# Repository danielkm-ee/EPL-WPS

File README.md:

# Spark EDM: An EDM power supply for hobby CNCs

A high-efficiency power supply unit designed for Electrical Discharge Machining (EDM) applications. The design is based on the Rack Robotics Powercore V3 and owes much to their engineering efforts.

## EPL Contributions

The EPL has reworked a few aspects of the Rack Robotics Powercore V3 for use in it's CNC-Type Wire EDM. Primarily, we've made use of 2.54mm pin headers in place of the spring-based connectors, or Pogo pins, to simplify construction without the enclosure. Other modifications have been made the the firmware project structure, separating sensor drivers, boost converter, fault handling, and other portions of the project into a modular C++ library. We have also implemented a frequency-coded feedback signal for compatibility with encoder and edge counting inputs available on many CNC control boards.

If you would like to explore or purchase the original PowerCore V3, please vist Rack Robotics at

and

# Repository Structure

```
├── docs               - documentation files & repository resources
│   ├── img                - images for README.md's
│   ├── LTSpice            - LTSpice Simulations
│   └── schematics         - pdfs of the schematics
├── firmware           - firmware project and library based on the PicoSDK
│   ├── docs               - docs for the firmware
│   ├── feedback_test      - firmware which outputs a frequency sweep for feedback testing
│   ├── src                - source files for the Spark EDM firmware
│   └── tpl0401b_test      - test firmware for testing the boost module potentiometer
├── hardware           - hardware resources for PCBs and the enclosure
│   ├── CAD                - CAD resources for enclosure design & system documentation
│   ├── circuit-boards     - circuit boards for the Spark EDM
│   └── KiCAD-library      - KiCAD library for the Spark EDM
└── tools              - tools for flashing & communicating with the Spark EDM
```

# Building the EDM Supply
The Spark EDM is not available for purchase through the EPL or any other means, but access to the manufacturing resources are provided for those with experience ordering and building up PCBs through the likes of JLCPCB, Oshpark, or PCBWay.

# LICENSE 
This project is based on Powercore V3 by Rack Robotics, Inc., used under CC BY-NC-SA 4.0.

Original copyright: © 2025 Rack Robotics, Inc.

Modifications and additions by Portland State University Electronics Prototyping Lab (PSU EPL) are also licensed under CC BY-NC-SA 4.0.

## Changes from Original
* Firmare:
    * Migration from Arduino to pure PicoSDK
    * new project structure and firmware documetation
    * frequency-coded feedback signal
    * testing firmware for the tpl10401b
    * tools for flashing and communicating with the device
    * extended command line interface with commands for setting the gap voltage and machining frequency
    * conventionalized responses from the serial interface for debugging
    * modularized library for the various functions of the power supply for extendability
    * fault handler and context management utilities
* Hardware:
    * Replacement of the RackRobotics and PowercoreV3 logo in compliance with copyright restrictions
    * Use of 2.54mm headers in place of spring-loaded connectors for ease of assembly
    * Removal of thermal reliefs on high-current capacitors in the pi-filter and boost converter module
    * Layout changes with larger trace widths for high current lines
    * Adaptations for 2.54mm connectors
    * Edge cutout for Pi Pico micro-USB and testpoints
    * Updated component values for missing JCL & digikey part numbers
* Documentation
    * Updated schematics reflecting changes in PCB implementation
    * Firmware documentation reflecting new library, developers manual, and coding conventions for maintenence and new feature introduction
    * Developer's notes from capstone members at Portland State University

## You are free to:
* Share — copy and redistribute the material in any medium or format
* Adapt — remix, transform, and build upon the material

### Under the following terms:
* **Attribution** — You must give appropriate credit, provide a link to the license, and indicate if changes were made
* **NonCommercial** — You may not use the material for commercial purposes
* **ShareAlike** — If you remix, transform, or build upon the material, you must distribute your contributions under the same license

For the full license text, see: https://creativecommons.org/licenses/by-nc-sa/4.0/

### Notices:
You do not have to comply with the license for elements of the material in the public domain or where your use is permitted by an applicable exception or limitation.

No warranties are given. The license may not give you all of the permissions necessary for your intended use. For example, other rights such as publicity, privacy, or moral rights may limit how you use the material.

For the full license text, see: https://creativecommons.org/licenses/by-nc-sa/4.0/

This includes all hardware designs, firmware, documentation, and associated files in this repository. Commercial use requires explicit written permission from the project maintainers.

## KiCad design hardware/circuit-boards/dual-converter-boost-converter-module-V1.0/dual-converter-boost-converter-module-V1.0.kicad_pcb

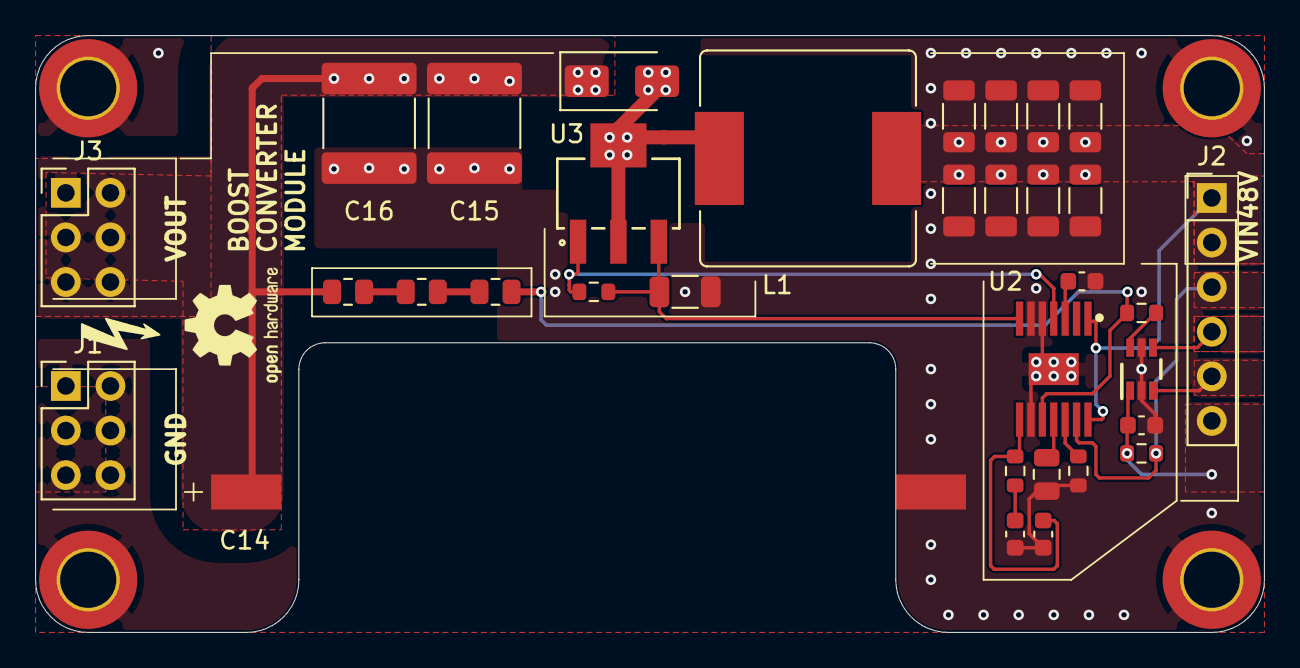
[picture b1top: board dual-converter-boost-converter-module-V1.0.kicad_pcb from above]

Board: 4 copper layers, 70.0 x 34.0 mm, 37 parts (0 on the bottom side), 19 nets.

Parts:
C1, C2, C3, C4, C6, C7, C8, C9: 10 uF; C_1206_3216Metric
C5, C10: 1 uF; C_0603_1608Metric
C11: 33 uF; C_0805_2012Metric
C12: 39nF; C_0603_1608Metric
C13: F; C_0603_1608Metric
C14: 22UF; 226TTA350M
C15, C16: 2.2 uF; C_2220_5750Metric
D1: US1M-13-F; D_SMA
H1, H2, H3, H4: M3_DIN; MountingHole_3.2mm_M3_DIN965_Pad_TopBottom
J1, J3: Vout Conn; PinHeader_2x03_P2.54mm_Vertical
J2: Conn_01x06; PinHeader_1x06_P2.54mm_Vertical
L1: 680 uH; SRR1210-681M
R1, R2, R3: 200K; R_0805_2012Metric
R4, R5: 2.2K; R_0603_1608Metric
R6: 49.3K; R_0603_1608Metric
R7: 15K; R_0603_1608Metric
R8: 100K; R_0603_1608Metric
R9: 90mR; R_1206_3216Metric
U1: TPL0401B-10DCKR
U2: LM5156HPWPR; lm5156h
U3: STN3N40K3

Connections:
+3.3V: C5.1, J2.6, R5.1, U1.1 (VDD)
+48V: C1.1, C2.1, C3.1, C4.1, C6.1, C7.1, C8.1, C9.1, J2.1, J2.2, L1.1, U2.1 (BIAS), U2.14 (EN_UVLO_SYNC)
/BOOST_PGOOD: J2.3, R5.2, U2.13 (PGOOD)
/BOOST_SWITCH_NET: D1.2 (A), L1.2, U3.2 (D), U3.4 (D)
/COMPENSATION: C13.1, R7.1, U2.8 (COMP)
/COUT_BOOST: C14.1, C15.1, C16.1, D1.1 (K), J3.1, J3.2, J3.3, J3.4, J3.5, J3.6, R1.1
/CURRENT_SENSE: R8.2, R9.1, U2.7 (CS), U3.3 (S)
/GATE_NET: R8.1, U2.4 (GATE), U3.1 (G)
/V_FEEDBACK: R3.2, R4.2, U2.10 (FB)
GND: C1.2, C2.2, C3.2, C4.2, C5.2, C6.2, C7.2, C8.2, C9.2, C10.2, C11.2, C12.2, C13.2, C14.2, C15.2, C16.2, H1.1, H2.1, H3.1, H4.1, J1.1, J1.2, J1.3, J1.4, J1.5, J1.6, R6.2, R9.2, U1.2 (GND), U1.5 (W), U2.5 (PGND), U2.6 (AGND), U2.9 (DITHOFF), U2.15 (EP)
unnamed: C12.1, R7.2
unnamed: J2.4, U1.4 (SDA)
unnamed: J2.5, U1.3 (SCL)
unnamed: R1.2, R2.1
unnamed: R2.2, R3.1
unnamed: R4.1, U1.6 (H)
unnamed: R6.1, U2.12 (RT)
unnamed: C11.1, U2.11 (SS)
unnamed: C10.1, U2.3 (VCC)

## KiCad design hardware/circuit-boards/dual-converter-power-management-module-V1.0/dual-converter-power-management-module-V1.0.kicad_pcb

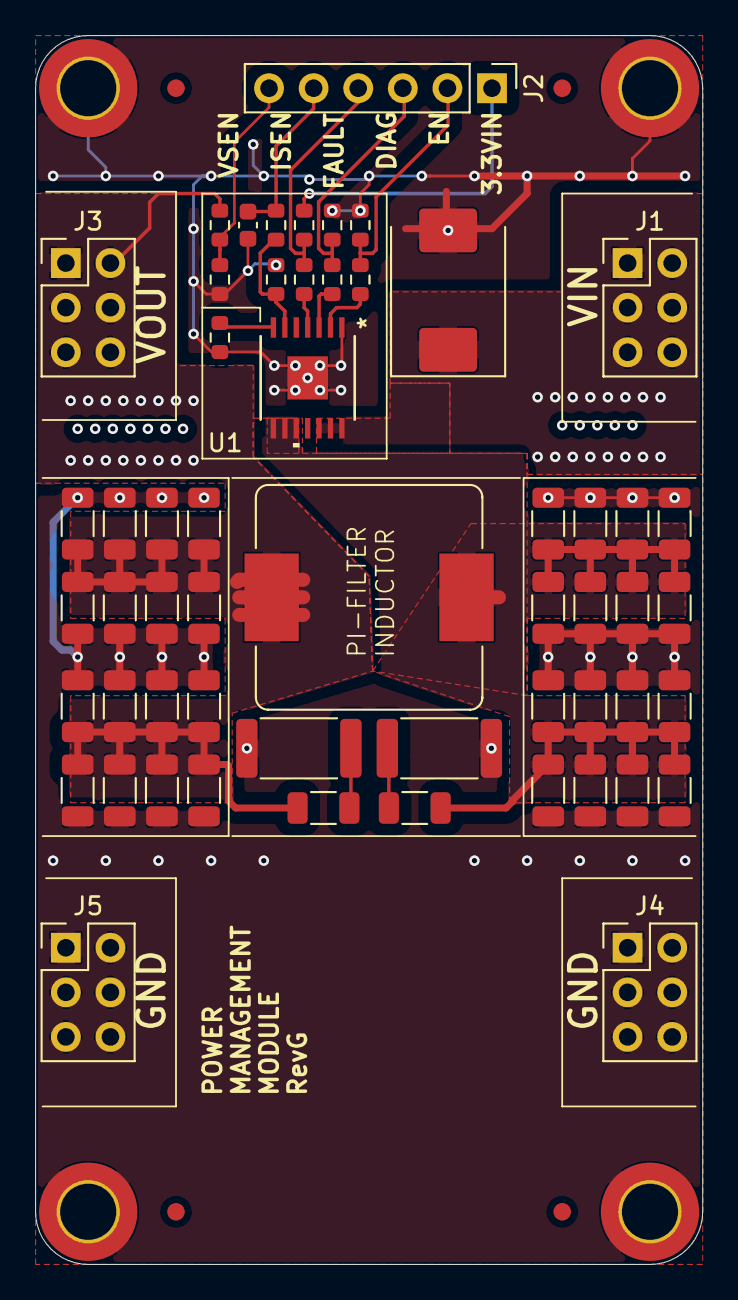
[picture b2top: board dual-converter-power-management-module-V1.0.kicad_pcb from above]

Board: 4 copper layers, 38.0 x 70.0 mm, 60 parts (0 on the bottom side), 17 nets.

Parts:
C1: 1 uF; C_0603_1608Metric
C2, C3, C4, C5, C6, C7, C8, C9, C10, C11, C12, C13, C14, C15, C16, C17, C18, C19, C20, C21, C22, C23, C24, C25, C26, C27, C28, C29, C30, C31, C32, C33, C34, C35: 10 uF; C_1206_3216Metric
D1: SMCJ60A-E3/57T; D_SMC
H1, H2, H3, H4: M3_DIN; MountingHole_3.2mm_M3_DIN965_Pad_TopBottom
J1, J3, J4, J5: Conn_02x03_Odd_Even; PinHeader_2x03_P2.54mm_Vertical
J2: Conn_01x06_Pin; PinHeader_1x06_P2.54mm_Vertical
L1: 18uH; SRP1245A
R1, R6, R7: 100K; R_0603_1608Metric
R2, R3, R4, R5: 2.2K; R_0603_1608Metric
R8: 249R; R_0603_1608Metric
R9: 0R; R_0603_1608Metric
R10, R13: 1R; R_2512_6332Metric
R11: 172K; R_0603_1608Metric
R12: 10K; R_0603_1608Metric
U1: TPS1HTC30AQPWPRQ1; TPS1HTC30-Q1

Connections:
+3.3V: J2.1, R1.1
+48V: C19.1, C20.1, C21.1, C22.1, C23.1, C24.1, C25.1, C26.1, C27.1, C28.1, C29.1, C30.1, C31.1, C32.1, C33.1, C34.1, C35.1, J3.1, J3.2, J3.3, J3.4, J3.5, J3.6, L1.2, R11.1
+48VIN: D1.1 (A1), J1.1, J1.2, J1.3, J1.4, J1.5, J1.6, U1.12 (VS), U1.13 (VS), U1.14 (VS)
/FILTER_IN: C2.1, C3.1, C4.1, C5.1, C6.1, C7.1, C8.1, C9.1, C10.1, C11.1, C12.1, C13.1, C14.1, C15.1, C16.1, C17.1, C18.1, L1.1, U1.8 (VOUT), U1.9 (VOUT), U1.10 (VOUT)
GND: C1.2, C2.2, C3.2, C4.2, C5.2, C6.2, C7.2, C8.2, C9.2, C11.2, C12.2, C13.2, C14.2, C15.2, C16.2, C17.2, C18.2, C19.2, C20.2, C21.2, C22.2, C23.2, C24.2, C25.2, C26.2, C28.2, C29.2, C30.2, C31.2, C32.2, C33.2, C34.2, C35.2, D1.2 (A2), H1.1, H2.1, H3.1, H4.1, J4.1, J4.2, J4.3, J4.4, J4.5, J4.6, J5.1, J5.2, J5.3, J5.4, J5.5, J5.6, R6.2, R7.2, R8.2, R9.2, R10.2, R12.2, R13.2, U1.1 (GND)
unnamed: C10.2, R10.1
unnamed: C27.2, R13.1
unnamed: J2.2, R2.1, R6.1
unnamed: J2.3, R3.1, R7.1
unnamed: J2.4, R1.2, R4.1
unnamed: C1.1, J2.5, R5.1
unnamed: R4.2, U1.4 (*FAULT)
unnamed: R3.2, U1.3 (DIAG_EN)
unnamed: R2.2, U1.2 (EN)
unnamed: R9.1, U1.7 (ILIM)
unnamed: R5.2, R8.1, U1.6 (SNS)
VSense: J2.6, R11.2, R12.1

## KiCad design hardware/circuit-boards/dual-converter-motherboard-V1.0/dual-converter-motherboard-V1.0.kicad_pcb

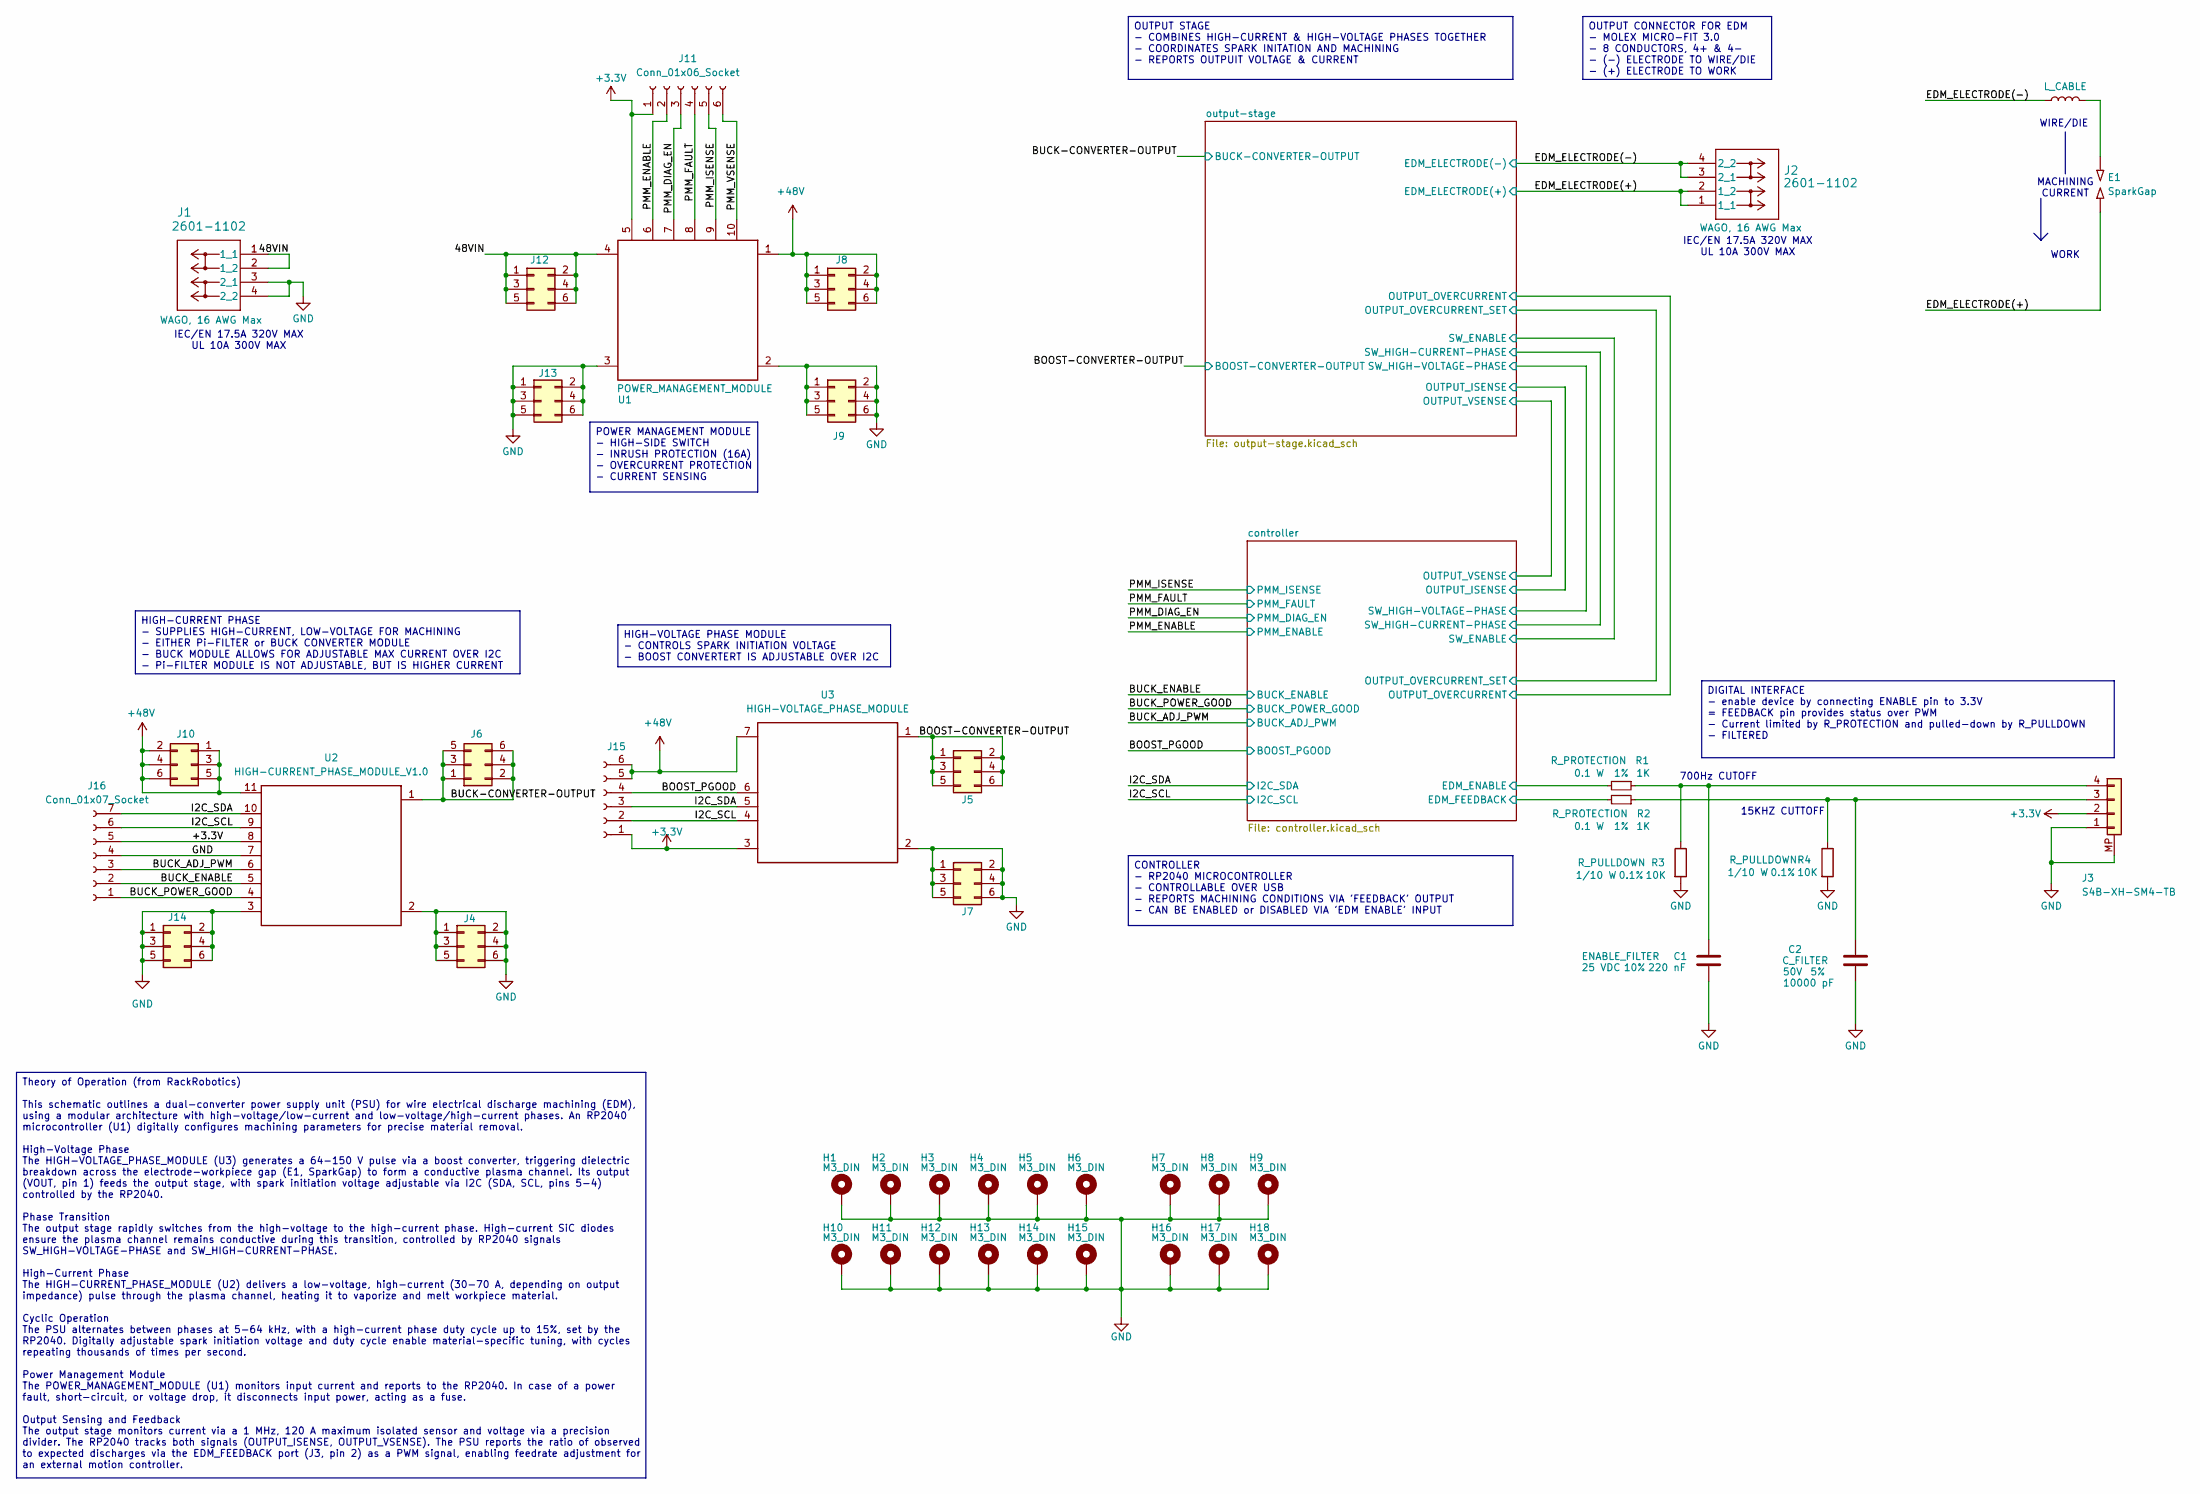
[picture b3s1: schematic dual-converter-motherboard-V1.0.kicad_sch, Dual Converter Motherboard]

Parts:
C1: 220 nF; C_0603_1608Metric; Tolerance 10%; Max Voltage 25 VDC; Manufacturer# AC0603KRX7R9BB224; LCSC Part # C726565
C2: 10000 pF; C_0603_1608Metric; Tolerance 5%; Max Voltage 50V; Manufacturer# CC0603JRX7R9BB103; LCSC Part # C115056
E1: SparkGap; NULL; Manufacturer# NULL; LCSC Part # NULL
H1, H2, H3, H4, H5, H6, H7, H8, H9, H10, H11, H12, H13, H14, H15, H16, H17, H18: M3_DIN; MountingHole_3.2mm_M3_DIN965_Pad_TopBottom; Manufacturer# NULL
J1, J2: 2601-1102; Manufacturer# 2601-1102; LCSC Part # C7509568
J3: S4B-XH-SM4-TB; Manufacturer# S4B-XH-SM4-TB; LCSC Part # C161861
J4, J5, J6, J7, J8, J9, J10, J12, J13, J14: Conn_02x03_Odd_Even; PinSocket_2x03_P2.54mm_Vertical
J11, J15: Conn_01x06_Socket; PinSocket_1x06_P2.54mm_Vertical
J16: Conn_01x07_Socket; PinSocket_1x07_P2.54mm_Vertical
L_CABLE1: L_CABLE
R1, R2: 1K; R_0603_1608Metric; Tolerance 1%; Manufacturer# RC0603FR-071KL; LCSC Part # C22548
R3, R4: 10K; R_0603_1608Metric; Tolerance 0.1%; Manufacturer# RC0603BR-0710KL; LCSC Part # C20161635
U1: POWER_MANAGEMENT_MODULE; POWER_MANAGEMENT_MODULE_FOOTPRINT_V1.0
U2: HIGH-CURRENT_PHASE_MODULE_V1.0; HIGH-CURRENT_PHASE_MODULE_FOOTPRINT_V1.0
U3: HIGH-VOLTAGE_PHASE_MODULE; HIGH-VOLTAGE_PHASE_MODULE_FOOTPRINT_V1.0

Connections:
+3.3V: J3.2, J11.1, J15.1, J16.5, U1.5, U2.8 (3.3VIN), U3.3 (GND); also elsewhere on the board
+48V: J8.1, J8.2, J8.3, J8.4, J8.5, J8.6, J10.1, J10.2, J10.3, J10.4, J10.5, J10.6, J15.5, J15.6, U1.1 (VOUT), U2.11 (48VIN), U3.7 (48VIN); also elsewhere on the board
/48VIN: J1.1 (1_1), J1.2 (1_2), J12.1, J12.2, J12.3, J12.4, J12.5, J12.6, U1.4 (VIN)
/BOOST-CONVERTER-OUTPUT: J5.1, J5.2, J5.3, J5.4, J5.5, J5.6, U3.1 (VOUT); also elsewhere on the board
/BOOST_PGOOD: J15.4, U3.6 (PGOOD); also elsewhere on the board
/BUCK-CONVERTER-OUTPUT: J6.1, J6.2, J6.3, J6.4, J6.5, J6.6, U2.1 (VOUT); also elsewhere on the board
/BUCK_ADJ_PWM: J16.3, U2.6 (PWM_ADJ); also elsewhere on the board
/BUCK_ENABLE: J16.2, U2.5 (ENABLE); also elsewhere on the board
/BUCK_POWER_GOOD: J16.1, U2.4 (PGOOD); also elsewhere on the board
/EDM_ELECTRODE(+): E1.1, J2.1 (1_1), J2.2 (1_2); also elsewhere on the board
/EDM_ELECTRODE(-): J2.3 (2_1), J2.4 (2_2), L_CABLE1.1; also elsewhere on the board
/I2C_SCL: J15.2, J16.6, U2.9 (SCL), U3.4 (SCL); also elsewhere on the board
/I2C_SDA: J15.3, J16.7, U2.10 (SDA), U3.5 (SDA); also elsewhere on the board
/PMM_DIAG_EN: J11.3, U1.7; also elsewhere on the board
/PMM_ENABLE: J11.2, U1.6; also elsewhere on the board
/PMM_FAULT: J11.4, U1.8; also elsewhere on the board
/PMM_ISENSE: J11.5, U1.9; also elsewhere on the board
/PMM_VSENSE: J11.6, U1.10
/controller/EDM_ENABLE: R1.2; also elsewhere on the board
/controller/EDM_FEEDBACK: R2.2; also elsewhere on the board
GND: C1.2, C2.2, H1.1, H2.1, H3.1, H4.1, H5.1, H6.1, H7.1, H8.1, H9.1, H10.1, H11.1, H12.1, H13.1, H14.1, H15.1, H16.1, H17.1, H18.1, J1.3 (2_1), J1.4 (2_2), J3.1, J3.MP, J4.1, J4.2, J4.3, J4.4, J4.5, J4.6, J7.1, J7.2, J7.3, J7.4, J7.5, J7.6, J9.1, J9.2, J9.3, J9.4, J9.5, J9.6, J13.1, J13.2, J13.3, J13.4, J13.5, J13.6, J14.1, J14.2, J14.3, J14.4, J14.5, J14.6, J16.4, R3.2, R4.2, U1.2, U1.3, U2.2 (GND), U2.3 (GND), U2.7 (GND), U3.2 (GND); also elsewhere on the board
unnamed: E1.2, L_CABLE1.2
unnamed: C2.1, J3.3, R2.1, R4.1
unnamed: C1.1, J3.4, R1.1, R3.1

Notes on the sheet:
IEC/EN 17.5A 320V MAX UL 10A 300V MAX
WORK
700Hz CUTOFF
MACHINING CURRENT
WIRE/DIE
15KHZ CUTTOFF
CONTROLLER - RP2040 MICROCONTROLLER - CONTROLLABLE OVER USB - REPORTS MACHINING CONDITIONS VIA 'FEEDBACK' OUTPUT - CAN BE ENABLED or DISABLED VIA 'EDM ENABLE' INPUT
HIGH-VOLTAGE PHASE MODULE - CONTROLS SPARK INITIATION VOLTAGE - BOOST CONVERTERT IS ADJUSTABLE OVER I2C
OUTPUT CONNECTOR FOR EDM - MOLEX MICRO-FIT 3.0 - 8 CONDUCTORS, 4+ & 4- - (-) ELECTRODE TO WIRE/DIE - (+) ELECTRODE TO WORK
HIGH-CURRENT PHASE - SUPPLIES HIGH-CURRENT, LOW-VOLTAGE FOR MACHINING - EITHER Pi-FILTER or BUCK CONVERTER MODULE - BUCK MODULE ALLOWS FOR ADJUSTABLE MAX CURRENT OVER I2C - Pi-FILTER MODULE IS NOT ADJUSTABLE, BUT IS HIGHER CURRENT
Theory of Operation (from RackRobotics) This schematic outlines a dual-converter power supply unit (PSU) for wire electrical discharge machining (EDM), using a modular architecture with high-voltage/low-current and low-voltage/high-current phases. An RP2040 microcontroller (U1) digitally configures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
OUTPUT STAGE - COMBINES HIGH-CURRENT & HIGH-VOLTAGE PHASES TOGETHER - COORDINATES SPARK INITATION AND MACHINING - REPORTS OUTPUIT VOLTAGE & CURRENT
POWER MANAGEMENT MODULE - HIGH-SIDE SWITCH - INRUSH PROTECTION (16A) - OVERCURRENT PROTECTION - CURRENT SENSING
DIGITAL INTERFACE - enable device by connecting ENABLE pin to 3.3V = FEEDBACK pin provides status over PWM - Current limited by R_PROTECTION and pulled-down by R_PULLDOWN - FILTERED

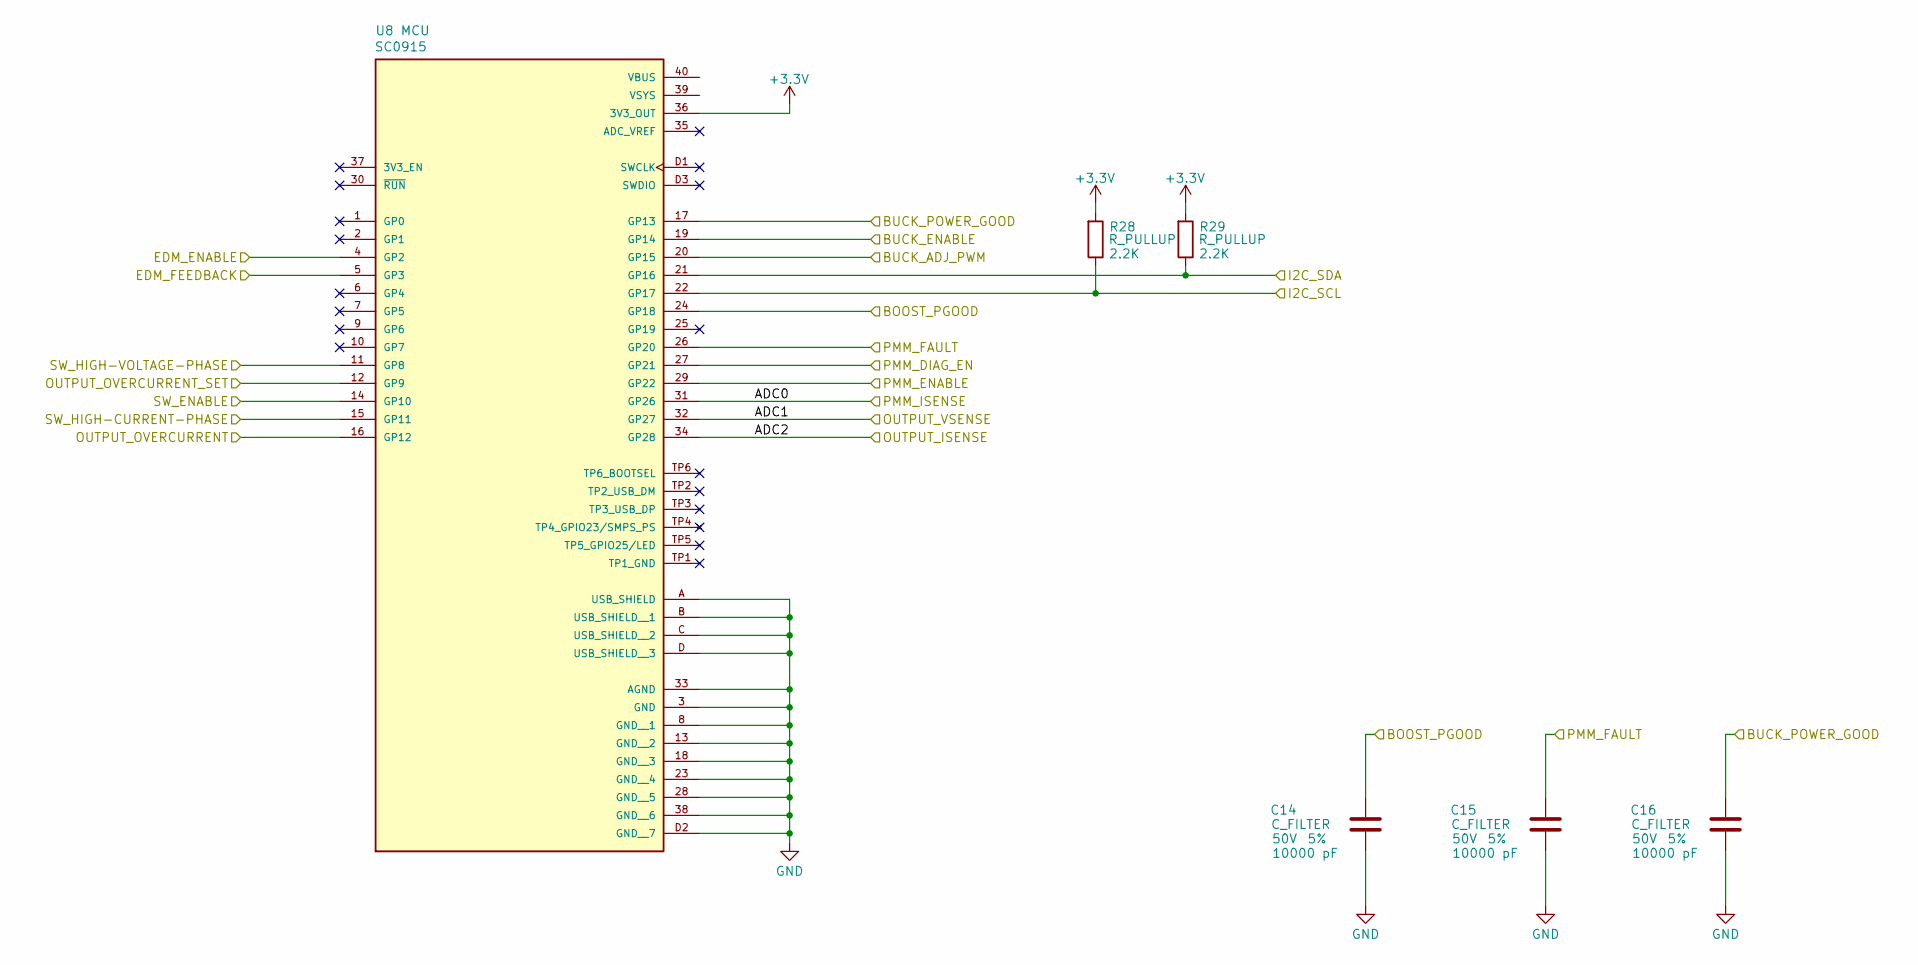
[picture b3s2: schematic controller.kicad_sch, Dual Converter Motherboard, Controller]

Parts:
C14, C15, C16: 10000 pF; C_0603_1608Metric; Tolerance 5%; Max Voltage 50V; Manufacturer# CC0603JRX7R9BB103; LCSC Part # C115056
R28, R29: 2.2K; R_0603_1608Metric; Tolerance 1%; Manufacturer# RC0603FR-132K2L; LCSC Part # C3032396
U8: SC0915; Manufacturer# SC0915; LCSC Part # C7203002

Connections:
+3.3V: R28.2, R29.2, U8.36 (3V3_OUT); also elsewhere on the board
/BOOST_PGOOD: C14.1, U8.24 (GP18); also elsewhere on the board
/BUCK_ADJ_PWM: U8.20 (GP15); also elsewhere on the board
/BUCK_ENABLE: U8.19 (GP14); also elsewhere on the board
/BUCK_POWER_GOOD: C16.1, U8.17 (GP13); also elsewhere on the board
/I2C_SCL: R28.1, U8.22 (GP17); also elsewhere on the board
/I2C_SDA: R29.1, U8.21 (GP16); also elsewhere on the board
/PMM_DIAG_EN: U8.27 (GP21); also elsewhere on the board
/PMM_ENABLE: U8.29 (GP22); also elsewhere on the board
/PMM_FAULT: C15.1, U8.26 (GP20); also elsewhere on the board
/PMM_ISENSE: U8.31 (GP26); also elsewhere on the board
/controller/ADC1: U8.32 (GP27); also elsewhere on the board
/controller/ADC2: U8.34 (GP28); also elsewhere on the board
/controller/EDM_ENABLE: U8.4 (GP2); also elsewhere on the board
/controller/EDM_FEEDBACK: U8.5 (GP3); also elsewhere on the board
/controller/OUTPUT_OVERCURRENT: U8.16 (GP12); also elsewhere on the board
/controller/OUTPUT_OVERCURRENT_SET: U8.12 (GP9); also elsewhere on the board
/controller/SW_ENABLE: U8.14 (GP10); also elsewhere on the board
/controller/SW_HIGH-CURRENT-PHASE: U8.15 (GP11); also elsewhere on the board
/controller/SW_HIGH-VOLTAGE-PHASE: U8.11 (GP8); also elsewhere on the board
GND: C14.2, C15.2, C16.2, U8.3 (GND), U8.8 (GND__1), U8.13 (GND__2), U8.18 (GND__3), U8.23 (GND__4), U8.28 (GND__5), U8.33 (AGND), U8.38 (GND__6), U8.A (USB_SHIELD), U8.B (USB_SHIELD__1), U8.C (USB_SHIELD__2), U8.D (USB_SHIELD__3), U8.D2 (GND__7); also elsewhere on the board

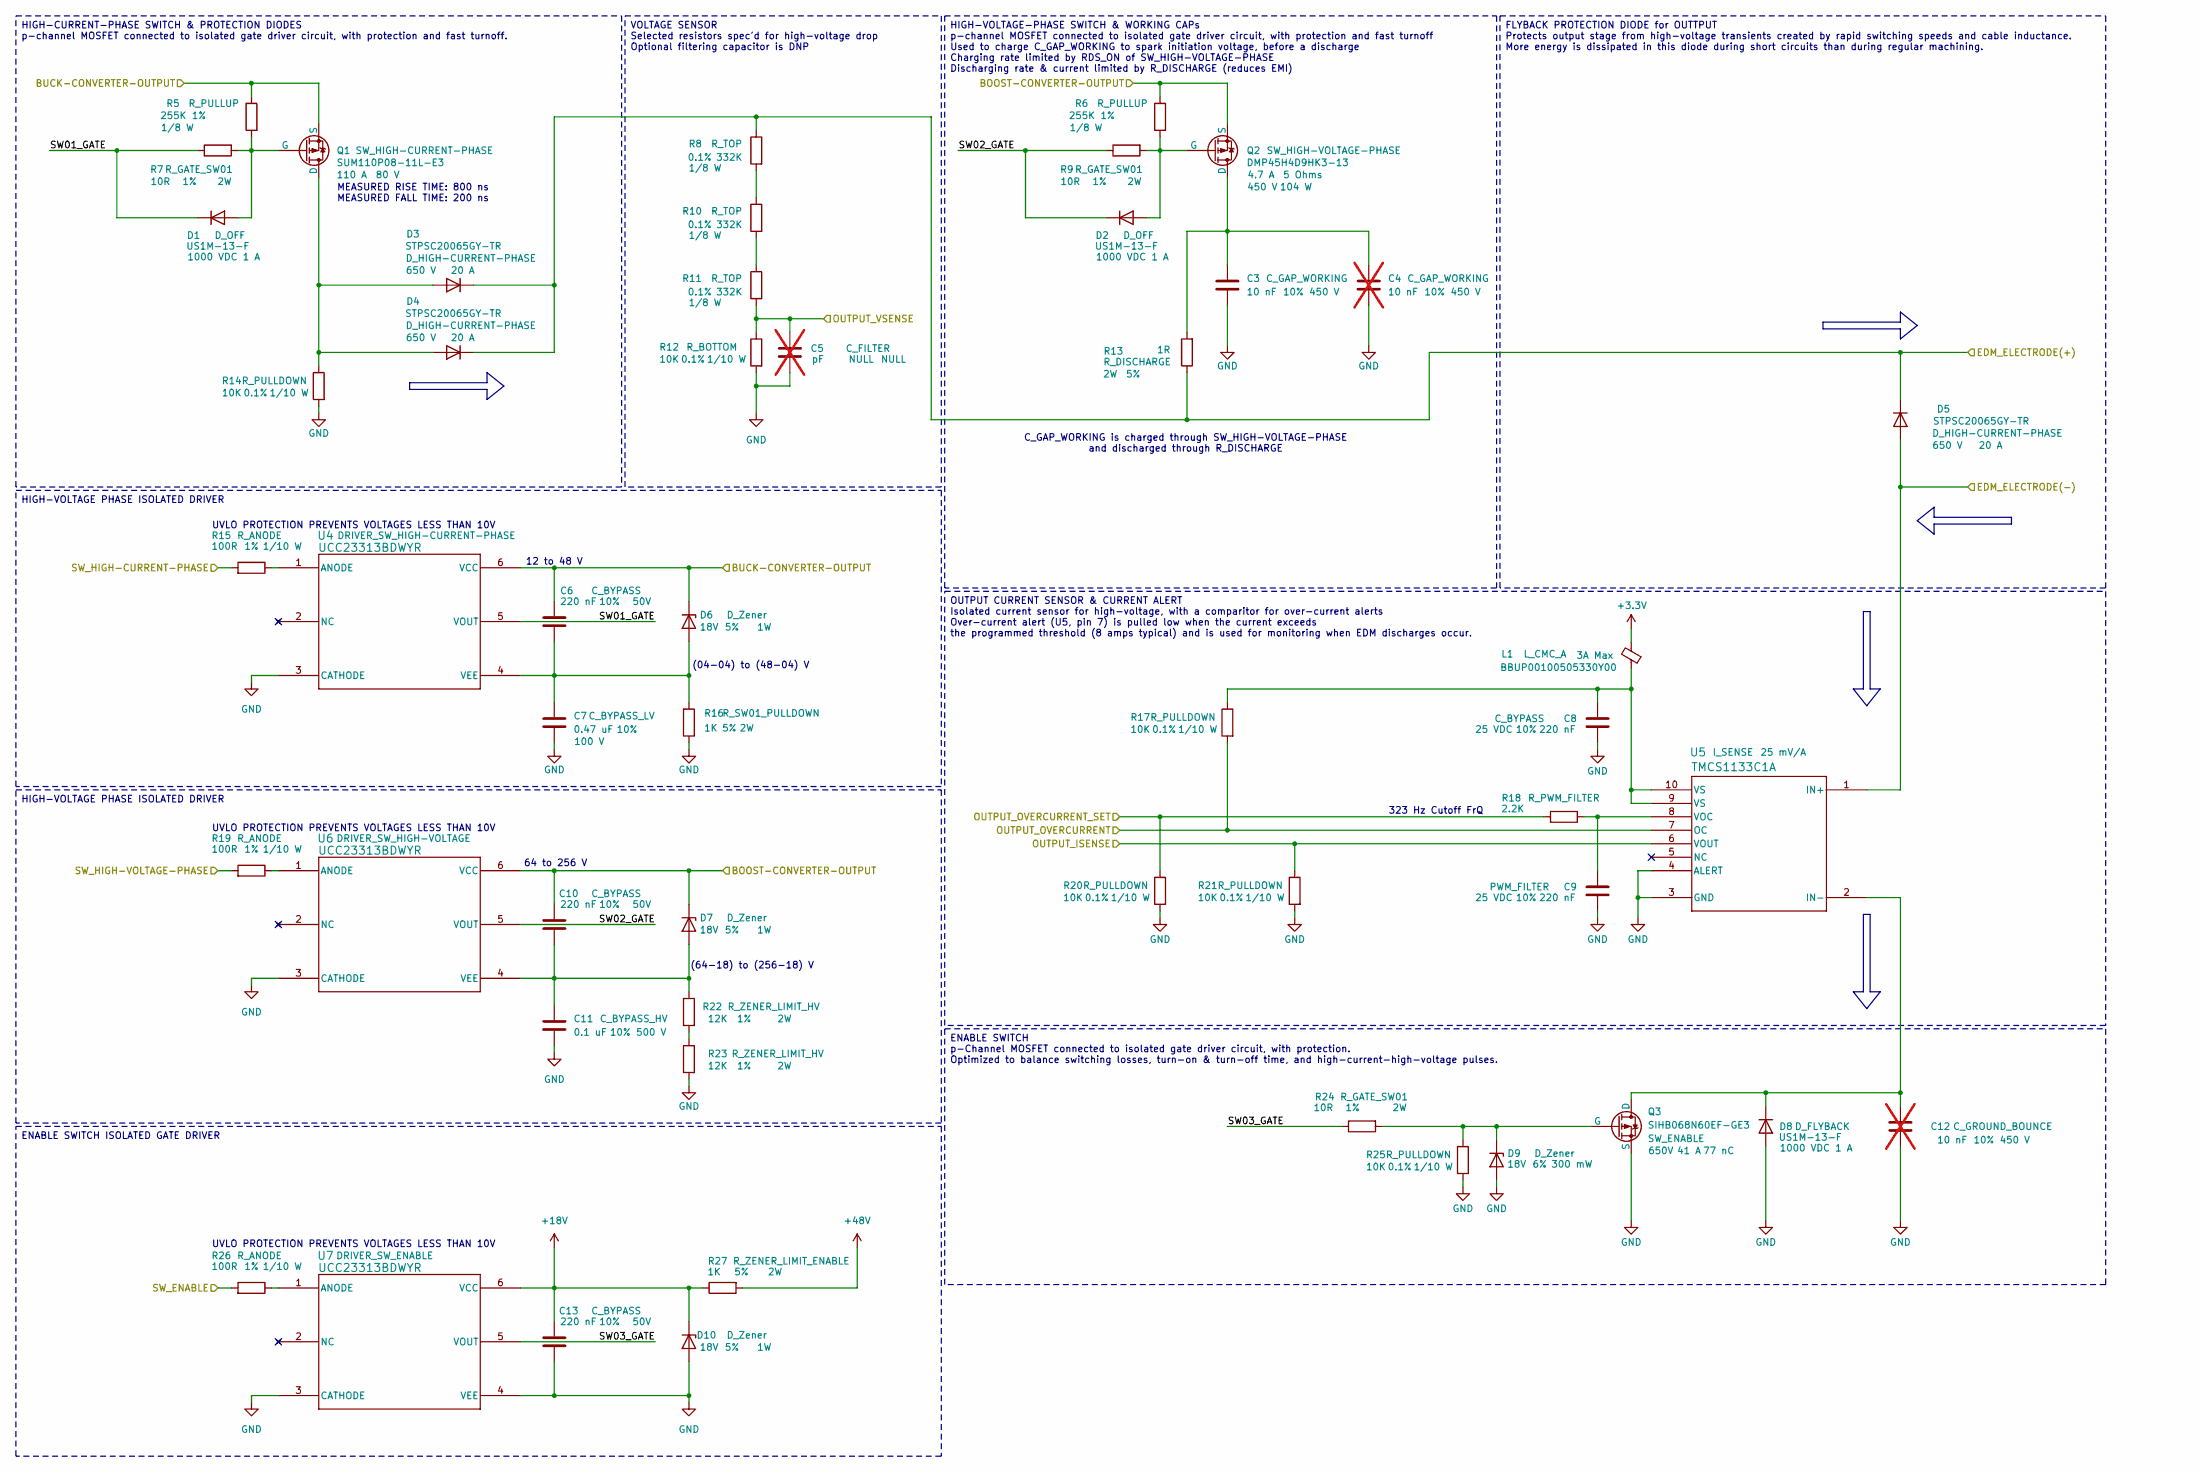
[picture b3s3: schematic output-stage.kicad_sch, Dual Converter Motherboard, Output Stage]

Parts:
C3: 10 nF; C_0805_2012Metric; Tolerance 10%; Max Voltage 450 V; Manufacturer# C2012X7T2W103K085AA; LCSC Part # C342860
C4, C12: 10 nF; C_0805_2012Metric; Tolerance 10%; Max Voltage 450 V; Manufacturer# C2012X7T2W103K085AA; LCSC Part # C342860; not fitted
C5: pF; C_0603_1608Metric; Tolerance NULL; Max Voltage NULL; Manufacturer# NULL; LCSC Part # NULL; not fitted
C6, C10, C13: 220 nF; C_0603_1608Metric; Tolerance 10%; Max Voltage 50V; Manufacturer# AC0603KRX7R9BB224; LCSC Part # C726565
C7: 0.47 uF; C_0805_2012Metric; Tolerance 10%; Max Voltage 100 V; Manufacturer# CC0805KKX7R0BB474; LCSC Part # C596323
C8, C9: 220 nF; C_0603_1608Metric; Tolerance 10%; Max Voltage 25 VDC; Manufacturer# AC0603KRX7R9BB224; LCSC Part # C726565
C11: 0.1 uF; C_1210_3225Metric; Tolerance 10%; Max Voltage 500 V; Manufacturer# C1210C104KCRACTU; LCSC Part # C141218
D1, D2, D8: US1M-13-F; D_SMA; Tolerance NULL; Manufacturer# US1M-13-F; LCSC Part # C99333
D3, D4, D5: STPSC20065GY-TR; Tolerance NULL; Manufacturer# STPSC20065GY-TR; LCSC Part # C2965441
D6, D7, D10: D_Zener; D_SMA; Zener Voltage 18V; Tolerance 5%; Manufacturer# SMAZ18-13-F; LCSC Part # C110525
D9: D_Zener; D_SOD-323; Zener Voltage 18V; Tolerance 6%; Manufacturer# MM3Z18VT1G; LCSC Part # C82043
L1: BBUP00100505330Y00; L_0402_1005Metric; Manufacturer# BLM15AX100SN1D; LCSC Part # C668299
Q1: SUM110P08-11L-E3; Max Voltage 80 V; Manufacturer# SUM110P08-11L-E3; LCSC Part # C2838509
Q2: DMP45H4D9HK3-13; Max Voltage 450 V; Manufacturer# DMP45H4D9HK3-13
Q3: SIHB068N60EF-GE3; TO-263-2; Max Voltage 650V; Manufacturer# SIHB068N60EF-GE3; LCSC Part # C3009875
R5, R6: 255K; R_0603_1608Metric; Tolerance 1%; Manufacturer# RC0603FR-07255KL; LCSC Part # C295887
R7, R9, R24: 10R; R_2512_6332Metric; Tolerance 1%; Manufacturer# SR2512JK-7W10RL
R8, R10, R11: 332K; R_0805_2012Metric; Tolerance 0.1%; Manufacturer# RT0805BRD07332KL
R12, R14, R17, R20, R21, R25: 10K; R_0603_1608Metric; Tolerance 0.1%; Manufacturer# RC0603BR-0710KL; LCSC Part # C20161635
R13: 1R; R_2512_6332Metric; Tolerance 5%; Manufacturer# CRM2512-JW-1R0ELF; LCSC Part # C840599
R15, R19, R26: 100R; R_0603_1608Metric; Tolerance 1%; Manufacturer# RC0603FR-10100RL; LCSC Part # C20161635
R16, R27: 1K; R_2512_6332Metric; Tolerance 5%; Manufacturer# RES 1K OHM 5% 2W 2512; LCSC Part # C7038808
R18: 2.2K; R_0603_1608Metric; Tolerance 1%; Manufacturer# RC0603FR-132K2L; LCSC Part # C3032396
R22, R23: 12K; R_2512_6332Metric; Tolerance 1%; Manufacturer# CRGP2512F12K; LCSC Part # C2082818
U4, U6, U7: UCC23313BDWYR; Tolerance NULL; Manufacturer# UCC23313BDWYR; LCSC Part # C2868027
U5: TMCS1133C1A; TMCS1133C3AQDVGR; Tolerance 1%; Manufacturer# TMCS1133C1AQDVGR; LCSC Part # C32266987

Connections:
+3.3V: L1.2; also elsewhere on the board
+18V: C13.1, D10.1 (K), R27.1, U7.6 (VCC)
+48V: R27.2; also elsewhere on the board
/BOOST-CONVERTER-OUTPUT: C10.1, D7.1 (K), Q2.3 (S), R6.1, U6.6 (VCC); also elsewhere on the board
/BUCK-CONVERTER-OUTPUT: C6.1, D6.1 (K), Q1.3 (S), R5.1, U4.6 (VCC); also elsewhere on the board
/EDM_ELECTRODE(+): D3.1 (K), D4.1 (K), D5.1 (K), R8.1, R13.1; also elsewhere on the board
/EDM_ELECTRODE(-): D5.2 (A), U5.1 (IN+); also elsewhere on the board
/controller/ADC1: C5.1, R11.2, R12.1; also elsewhere on the board
/controller/ADC2: R21.1, U5.6 (VOUT); also elsewhere on the board
/controller/OUTPUT_OVERCURRENT: R17.2, U5.7 (OC); also elsewhere on the board
/controller/OUTPUT_OVERCURRENT_SET: R18.1, R20.1; also elsewhere on the board
/controller/SW_ENABLE: R26.2; also elsewhere on the board
/controller/SW_HIGH-CURRENT-PHASE: R15.2; also elsewhere on the board
/controller/SW_HIGH-VOLTAGE-PHASE: R19.2; also elsewhere on the board
/output-stage/SW01_GATE: D1.1 (K), R7.1, U4.5 (VOUT)
/output-stage/SW02_GATE: D2.1 (K), R9.1, U6.5 (VOUT)
/output-stage/SW03_GATE: R24.1, U7.5 (VOUT)
GND: C3.2, C4.2, C5.2, C7.2, C8.2, C9.2, C11.2, C12.2, C13.2, D8.2 (A), D9.2 (A), D10.2 (A), Q3.3 (S), R12.2, R14.2, R16.1, R20.2, R21.2, R23.2, R25.2, U4.3 (CATHODE), U5.3 (GND), U5.4 (ALERT), U6.3 (CATHODE), U7.3 (CATHODE), U7.4 (VEE); also elsewhere on the board
unnamed: C8.1, L1.1, R17.1, U5.9 (VS), U5.10 (VS)
unnamed: D1.2 (A), Q1.2 (G), R5.2, R7.2
unnamed: D2.2 (A), Q2.2 (G), R6.2, R9.2
unnamed: D3.2 (A), D4.2 (A), Q1.1 (D), R14.1
unnamed: C6.2, C7.1, D6.2 (A), R16.2, U4.4 (VEE)
unnamed: C10.2, C11.1, D7.2 (A), R22.1, U6.4 (VEE)
unnamed: C12.1, D8.1 (K), Q3.2 (D), U5.2 (IN-)
unnamed: D9.1 (K), Q3.1 (G), R24.2, R25.1
unnamed: C3.1, C4.1, Q2.1 (D), R13.2
unnamed: R8.2, R10.1
unnamed: R10.2, R11.1
unnamed: R22.2, R23.1
unnamed: R15.1, U4.1 (ANODE)
unnamed: C9.1, R18.2, U5.8 (VOC)
unnamed: R19.1, U6.1 (ANODE)
unnamed: R26.1, U7.1 (ANODE)

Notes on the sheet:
UVLO PROTECTION PREVENTS VOLTAGES LESS THAN 10V
C_GAP_WORKING is charged through SW_HIGH-VOLTAGE-PHASE and discharged through R_DISCHARGE
323 Hz Cutoff FrQ
(04-04) to (48-04) V
12 to 48 V
(64-18) to (256-18) V
64 to 256 V
MEASURED RISE TIME: 800 ns MEASURED FALL TIME: 200 ns
FLYBACK PROTECTION DIODE for OUTTPUT Protects output stage from high-voltage transients created by rapid switching speeds and cable inductance. More energy is dissipated in this diode during short circuits than during regular machining.
HIGH-VOLTAGE PHASE ISOLATED DRIVER
ENABLE SWITCH ISOLATED GATE DRIVER
ENABLE SWITCH p-Channel MOSFET connected to isolated gate driver circuit, with protection. Optimized to balance switching losses, turn-on & turn-off time, and high-current-high-voltage pulses.
HIGH-VOLTAGE-PHASE SWITCH & WORKING CAPs p-channel MOSFET connected to isolated gate driver circuit, with protection and fast turnoff Used to charge C_GAP_WORKING to spark initiation voltage, before a discharge Charging rate limited by RDS_ON of SW_HIGH-VOLTAGE-PHASE Discharging rate & current limi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
OUTPUT CURRENT SENSOR & CURRENT ALERT Isolated current sensor for high-voltage, with a comparitor for over-current alerts Over-current alert (U5, pin 7) is pulled low when the current exceeds the programmed threshold (8 amps typical) and is used for monitoring when EDM discharges occur.
VOLTAGE SENSOR Selected resistors spec'd for high-voltage drop Optional filtering capacitor is DNP
HIGH-CURRENT-PHASE SWITCH & PROTECTION DIODES p-channel MOSFET connected to isolated gate driver circuit, with protection and fast turnoff.
